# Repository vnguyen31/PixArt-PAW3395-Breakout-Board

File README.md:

# PixArt-PAW3395-Breakout-Board
Fully functioning Breakout Board with SPI pin headers for PAW3395 Motion Sensor using KiCad and datasheet provided by PixArt
## Schematics

## PCB layout

## 3D viewer

## Ordering Information
You can upload the PCB file straight to OSHPARK and it will process the file and give you a price and PCB dimensions. As for parts, please refer to .csv file for BOM

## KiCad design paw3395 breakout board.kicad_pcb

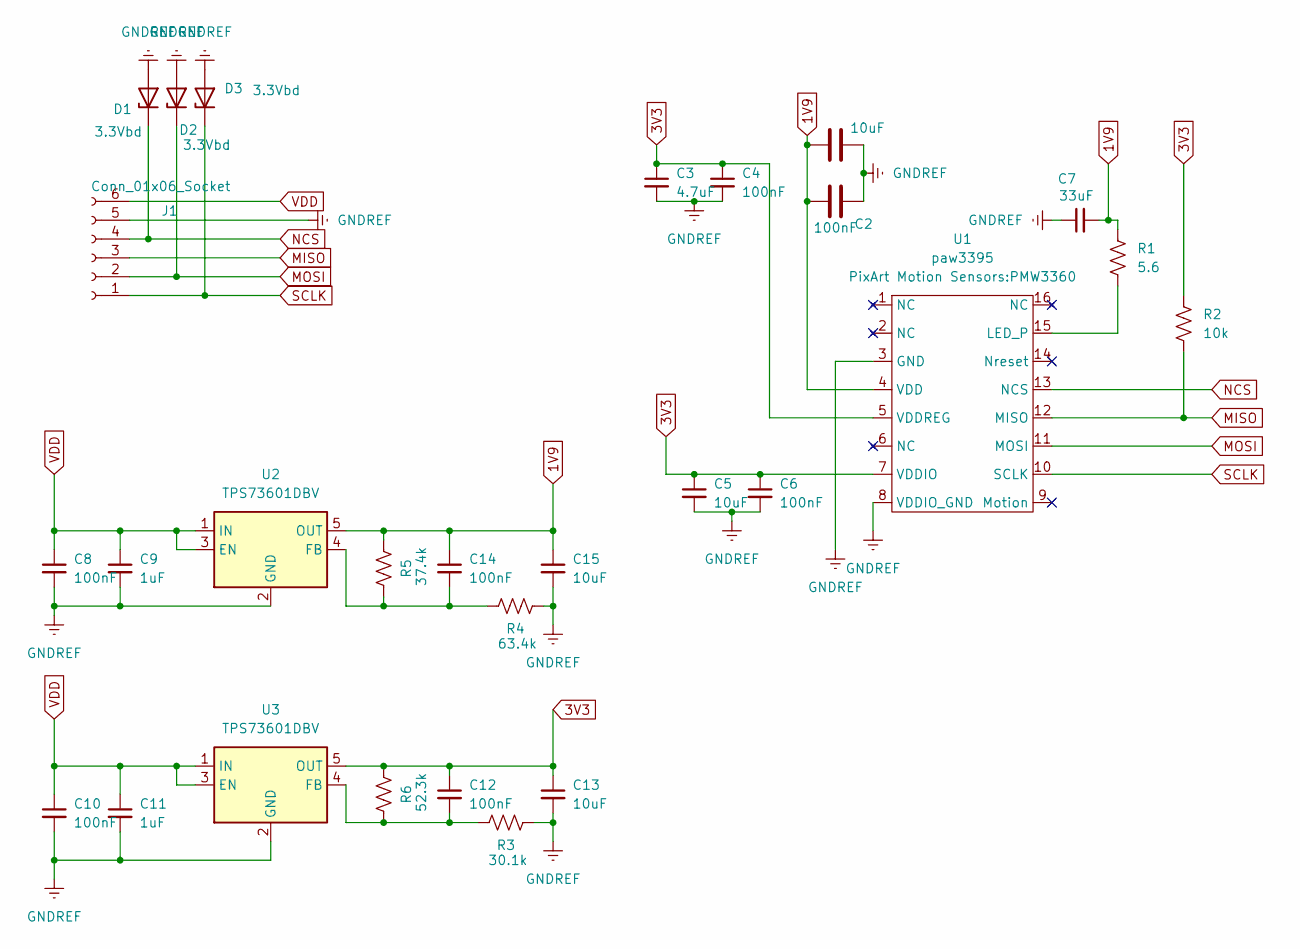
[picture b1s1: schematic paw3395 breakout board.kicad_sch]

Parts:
C1, C5, C13, C15: 10uF; C_0805_2012Metric
C2, C4, C6, C8, C10, C12, C14: 100nF; C_0805_2012Metric
C3: 4.7uF; C_0805_2012Metric
C7: 33uF; C_0805_2012Metric
C9, C11: 1uF; C_0805_2012Metric
D1, D2, D3: 3.3Vbd; D_SOD-323
J1: Conn_01x06_Socket; PinSocket_1x06_P2.54mm_Vertical
R1: 5.6; R_0805_2012Metric
R2: 10k; R_0805_2012Metric
R3: 30.1k; R_0805_2012Metric
R4: 63.4k; R_0805_2012Metric
R5: 37.4k; R_0805_2012Metric
R6: 52.3k; R_0805_2012Metric
U1: paw3395; PMW3360
U2, U3: TPS73601DBV; SOT-23-5

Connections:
1V9: C1.1, C2.1, C7.2, C14.1, C15.1, R1.1, R5.1, U1.4 (VDD), U2.5 (OUT)
3V3: C3.1, C4.1, C5.1, C6.1, C12.1, C13.1, R2.1, R6.1, U1.5 (VDDREG), U1.7 (VDDIO), U3.5 (OUT)
GNDREF: C1.2, C2.2, C3.2, C4.2, C5.2, C6.2, C7.1, C8.2, C9.2, C10.2, C11.2, C13.2, C15.2, D1.2 (A), D2.2 (A), D3.2 (A), J1.5, R3.1, R4.1, U1.3 (GND), U1.8 (VDDIO_GND), U2.2 (GND), U3.2 (GND)
MISO: J1.3, R2.2, U1.12 (MISO)
MOSI: D2.1 (K), J1.2, U1.11 (MOSI)
NCS: D1.1 (K), J1.4, U1.13 (NCS)
unnamed: R1.2, U1.15 (LED_P)
unnamed: C14.2, R4.2, R5.2, U2.4 (FB)
unnamed: C12.2, R3.2, R6.2, U3.4 (FB)
SCLK: D3.1 (K), J1.1, U1.10 (SCLK)
VDD: C8.1, C9.1, C10.1, C11.1, J1.6, U2.1 (IN), U2.3 (EN), U3.1 (IN), U3.3 (EN)

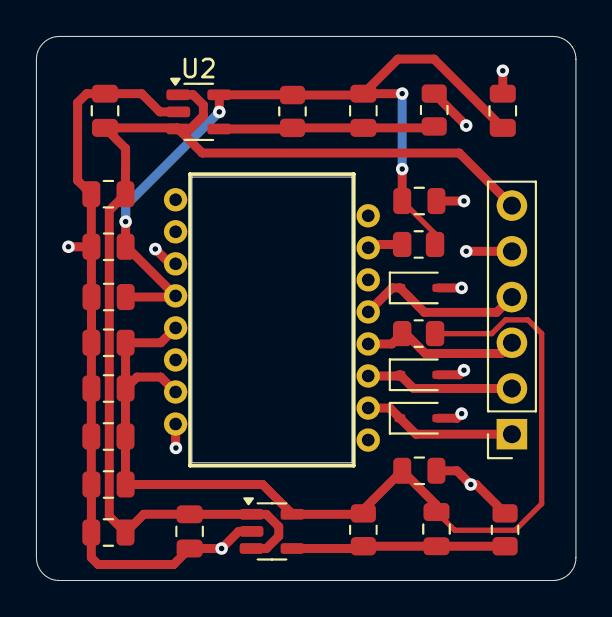
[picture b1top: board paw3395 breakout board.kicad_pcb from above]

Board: 2 copper layers, 30.0 x 30.2 mm, 28 parts (0 on the bottom side), 11 nets.
